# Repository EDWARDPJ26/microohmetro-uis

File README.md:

# Micro-ohmímetro de precisión (1 mΩ – 1 Ω) — versión 2

Proyecto de la asignatura **Diseño de Sistemas Electrónicos** de la Universidad Industrial de Santander (E3T), dictada por el profesor Jaime Barrero.
Autores: **Edward Andrés Pacheco Jurado** (2222236) y **Joseph Thomas Albarracín Contreras** (2220415), 2026.

Es un instrumento portátil con medición Kelvin de 4 hilos. Usa **corriente pulsada de dos niveles (1,042 A / 0,502 A)** y **medición ratiométrica**, con un ADC sigma-delta **AD7124-4** que aprovecha su PGA. El control lo hace un **ESP32-C3**, con BLE y OTA. Se alimenta de una **LiPo 1S de 2000 mAh** integrada en la PCB, que se carga por **USB-C Power Delivery** con un **BQ25895**.

## Contenido del repositorio
| Carpeta | Contenido |
|---|---|
| [`informe/`](informe/) | **Informe final** en PDF y su fuente LaTeX (`main.tex` y figuras) |
| [`hardware/kicad/`](hardware/kicad/) | Proyecto KiCad 10: esquemático jerárquico de 9 hojas, PCB de 4 capas, librería propia y scripts generadores (`gen/`) |
| [`hardware/fabricacion/`](hardware/fabricacion/) | Gerbers con taladros (ZIP), archivo de posiciones (pick & place) y modelo **STEP** |
| [`simulaciones/`](simulaciones/) | Netlists PSpice (`.cir`, `circuito_v2.inc`), datos `.csv` y resumen de resultados |
| [`imagenes/`](imagenes/) | Esquemáticos en SVG/PDF, renders 3D, plano acotado y capas de cobre |
| [`docs/`](docs/) | Diseño detallado (B1), BOM, resumen del esquemático (B3) e informes de las etapas 1–7 |

## Cómo abrir y verificar
- **Esquemático y PCB:** abrir `hardware/kicad/microohmetro_v2.kicad_pro` en **KiCad 10**. La librería propia se carga sola desde `Librerias/` gracias a `sym-lib-table`.
- **Regenerar el esquemático o la PCB:** `python gen/gen_sch3.py` y `python gen/gen_pcb.py`, con el Python que trae KiCad.
- **Simulaciones:** `psp_cmd.exe <archivo>.cir` (Cadence PSpice 22.1). **Los modelos de TI no se redistribuyen**; descárgalos y colócalos en `simulaciones/modelos/`:
  - OPA4388 (equivalente al OPA388): https://www.ti.com/lit/zip/sbomaz6 → `modelos/opa4388_pspice/OPA4388.LIB`
  - INA181A1: https://www.ti.com/lit/zip/sbombb7 → `modelos/ina181a1_pspice/ina181a1.lib`
- **Informe:** subir `informe/` a Overleaf (pdfLaTeX).

## Resultados principales
| Ítem | Valor |
|---|---|
| Error DC ratiométrico simulado | −0,0054 % (sistemático, se calibra) |
| FEM de ±10 µV | ±0,96 % con un nivel → **0 %** con dos niveles |
| Montecarlo, shunt 0,1 % | σ = **0,057 %** (diseño anterior: σ = 88 %) |
| PCB | 4 capas, **64 × 116 mm**, batería en la cara inferior |

**Estado de la PCB:** el DRC no reporta cortocircuitos ni violaciones de holgura. Quedan **unas 7 conexiones cortas por rutear** a mano antes de fabricar: VBUS_C, +3V3, SYS, PMID e I2C_SDA.

## Datasheets de los componentes principales
- [AD7124-4](https://www.analog.com/media/en/technical-documentation/data-sheets/ad7124-4.pdf)
- [REF3325](https://www.ti.com/lit/ds/symlink/ref3325.pdf)
- [OPA388](https://www.ti.com/lit/ds/symlink/opa388.pdf)
- [INA181](https://www.ti.com/lit/ds/symlink/ina181.pdf)
- [BQ25895](https://www.ti.com/lit/ds/symlink/bq25895.pdf)
- [STUSB4500](https://www.st.com/resource/en/datasheet/stusb4500.pdf)
- [ESP32-C3-WROOM-02](https://www.espressif.com/sites/default/files/documentation/esp32-c3-wroom-02_datasheet_en.pdf)
- [AP2112](https://www.diodes.com/assets/Datasheets/AP2112.pdf)
- [NTD25P03L](https://www.onsemi.com/pdf/datasheet/ntd25p03l-d.pdf)
- [WSK2512](https://www.vishay.com/docs/30108/wsk2512.pdf)
- [AO3401A](https://www.aosmd.com/res/datasheets/AO3401A.pdf)
- [USBLC6-2](https://www.st.com/resource/en/datasheet/usblc6-2.pdf)

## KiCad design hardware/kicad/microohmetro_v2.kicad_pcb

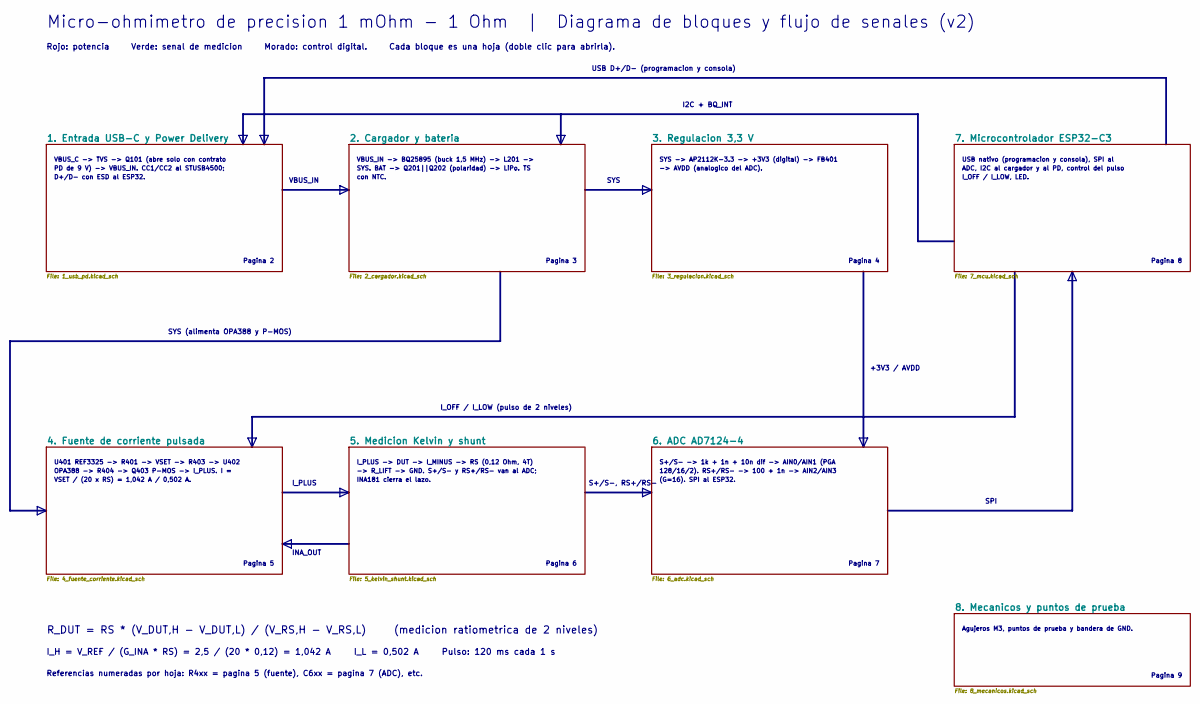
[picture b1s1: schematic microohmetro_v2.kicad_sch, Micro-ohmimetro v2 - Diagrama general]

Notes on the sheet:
VBUS_C -> TVS -> Q101 (abre solo con contrato
PD de 9 V) -> VBUS_IN. CC1/CC2 al STUSB4500;
D+/D- con ESD al ESP32.
Pagina 2
VBUS_IN -> BQ25895 (buck 1,5 MHz) -> L201 ->
SYS. BAT -> Q201||Q202 (polaridad) -> LiPo. TS
con NTC.
Pagina 3
SYS -> AP2112K-3.3 -> +3V3 (digital) -> FB401
-> AVDD (analogico del ADC).
Pagina 4
U401 REF3325 -> R401 -> VSET -> R403 -> U402
OPA388 -> R404 -> Q403 P-MOS -> I_PLUS. I =
VSET / (20 x RS) = 1,042 A / 0,502 A.
Pagina 5
I_PLUS -> DUT -> I_MINUS -> RS (0,12 Ohm, 4T)
-> R_LIFT -> GND. S+/S- y RS+/RS- van al ADC;
INA181 cierra el lazo.
Pagina 6
S+/S- -> 1k + 1n + 10n dif -> AIN0/AIN1 (PGA
128/16/2). RS+/RS- -> 100 + 1n -> AIN2/AIN3
(G=16). SPI al ESP32.
Pagina 7
USB nativo (programacion y consola), SPI al
ADC, I2C al cargador y al PD, control del pulso
I_OFF / I_LOW, LED.
Pagina 8
Agujeros M3, puntos de prueba y bandera de GND.
Pagina 9
VBUS_IN
SYS
SYS (alimenta OPA388 y P-MOS)
+3V3 / AVDD
I_PLUS
INA_OUT
S+/S-, RS+/RS-
SPI
I_OFF / I_LOW (pulso de 2 niveles)
I2C + BQ_INT
USB D+/D- (programacion y consola)

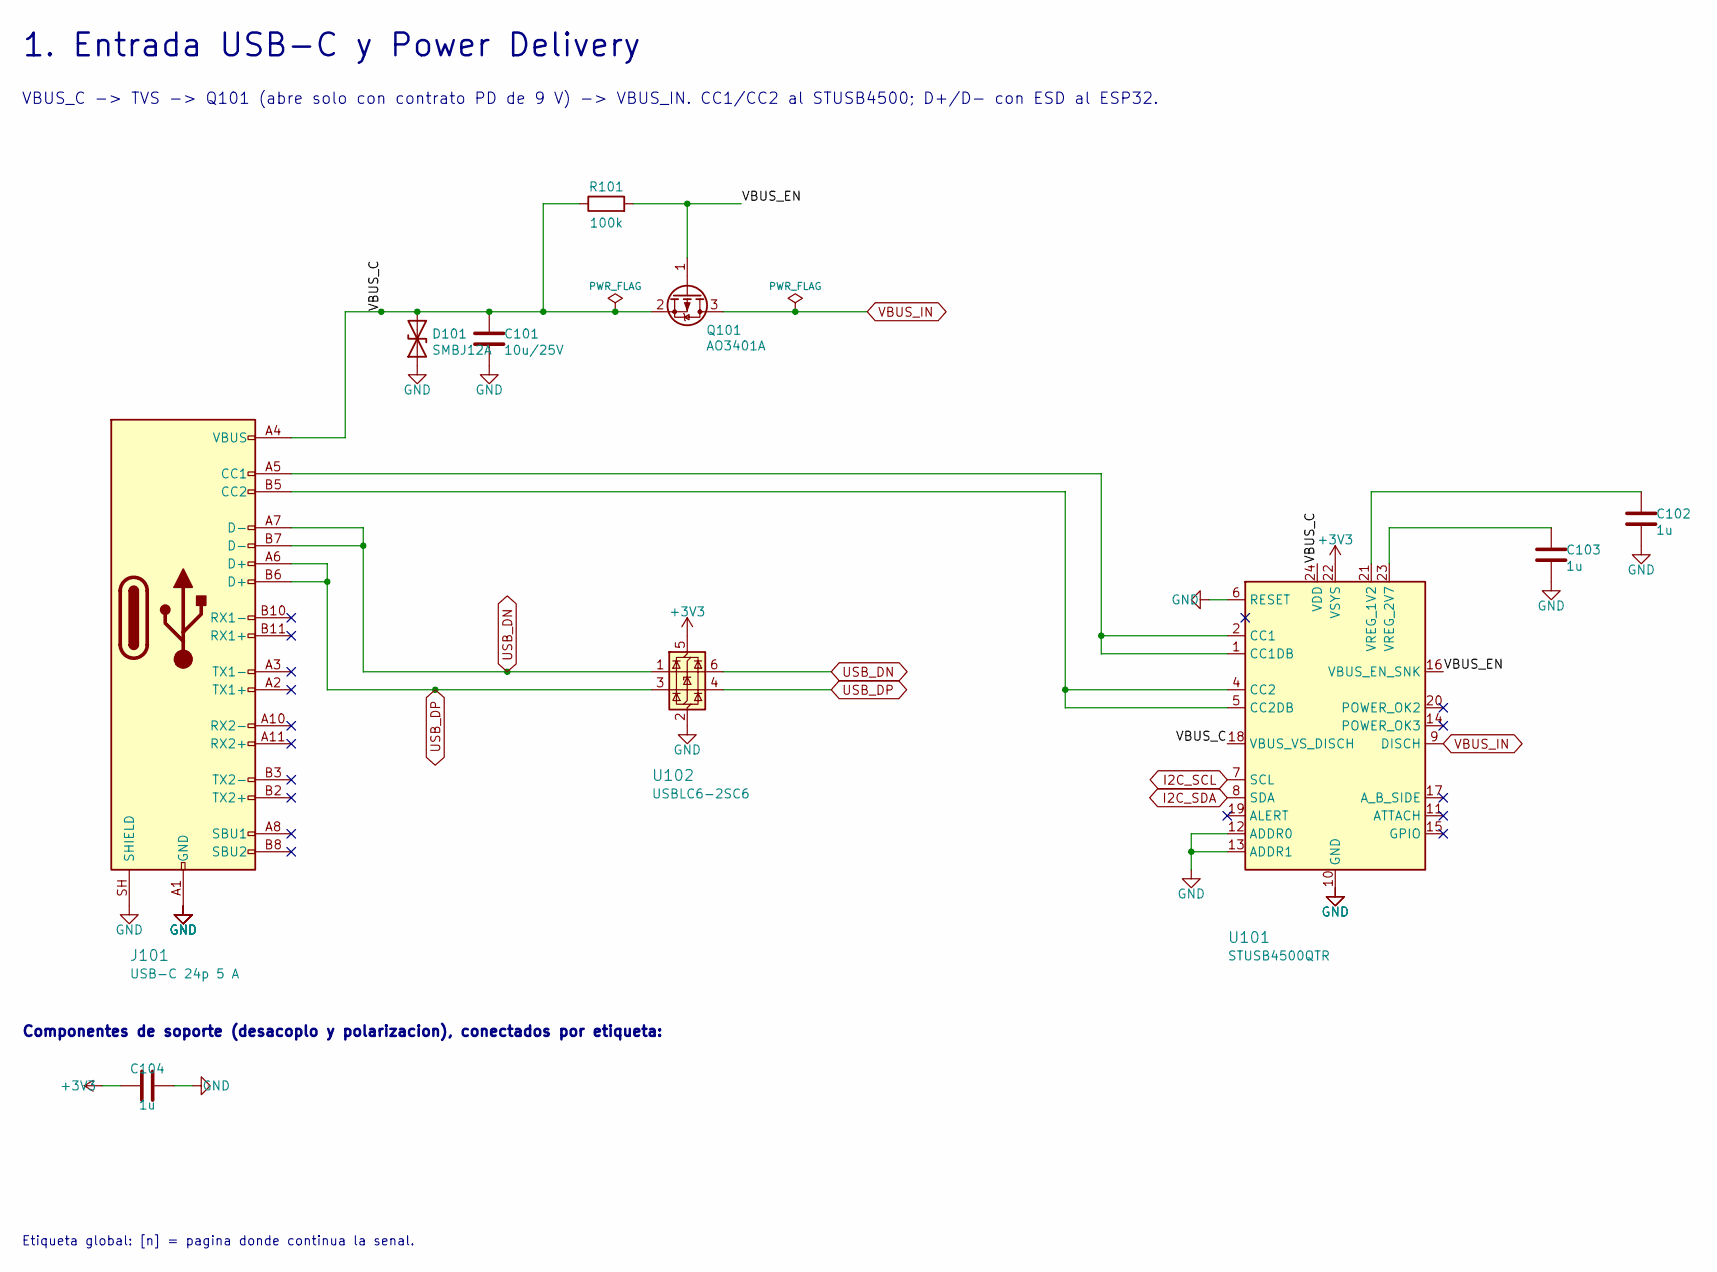
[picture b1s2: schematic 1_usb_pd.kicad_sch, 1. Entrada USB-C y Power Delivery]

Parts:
C101: 10u/25V; C_0805_2012Metric
C102, C103, C104: 1u; C_0603_1608Metric
D101: SMBJ12A; D_SMB; MPN SMBJ12A
J101: USB-C 24p 5 A; USB_C_Receptacle_Amphenol_12401610E4-2A; MPN Amphenol 12401610E4#2A
Q101: AO3401A; SOT-23; MPN AO3401A
R101: 100k; R_0603_1608Metric
U101: STUSB4500QTR; QFN-24-1EP_4x4mm_P0.5mm_EP2.7x2.7mm; MPN STUSB4500QTR
U102: USBLC6-2SC6; SOT-23-6; MPN USBLC6-2SC6

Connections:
+3V3: C104.1, U101.22 (VSYS), U102.5 (VBUS); also elsewhere on the board
GND: C101.2, C102.2, C103.2, C104.2, D101.1 (A1), J101.A1 (GND), J101.A12 (GND), J101.B1 (GND), J101.B12 (GND), J101.SH (SHIELD), U101.6 (RESET), U101.10 (GND), U101.12 (ADDR0), U101.13 (ADDR1), U101.25 (GND), U102.2 (GND); also elsewhere on the board
I2C_SCL: U101.7 (SCL); also elsewhere on the board
I2C_SDA: U101.8 (SDA); also elsewhere on the board
unnamed: J101.A5 (CC1), U101.1 (CC1DB), U101.2 (CC1)
unnamed: J101.B5 (CC2), U101.4 (CC2), U101.5 (CC2DB)
unnamed: C102.1, U101.21 (VREG_1V2)
unnamed: C103.1, U101.23 (VREG_2V7)
USB_DN: J101.A7 (D-), J101.B7 (D-), U102.1 (I/O1), U102.6 (I/O1); also elsewhere on the board
USB_DP: J101.A6 (D+), J101.B6 (D+), U102.3 (I/O2), U102.4 (I/O2); also elsewhere on the board
VBUS_C: C101.1, D101.2 (A2), J101.A4 (VBUS), J101.A9 (VBUS), J101.B4 (VBUS), J101.B9 (VBUS), Q101.2 (S), R101.1, U101.18 (VBUS_VS_DISCH), U101.24 (VDD)
VBUS_EN: Q101.1 (G), R101.2, U101.16 (VBUS_EN_SNK)
VBUS_IN: Q101.3 (D), U101.9 (DISCH); also elsewhere on the board

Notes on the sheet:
1. Entrada USB-C y Power Delivery
VBUS_C -> TVS -> Q101 (abre solo con contrato PD de 9 V) -> VBUS_IN. CC1/CC2 al STUSB4500; D+/D- con ESD al ESP32.
Componentes de soporte (desacoplo y polarizacion), conectados por etiqueta:
Etiqueta global: [n] = pagina donde continua la senal.

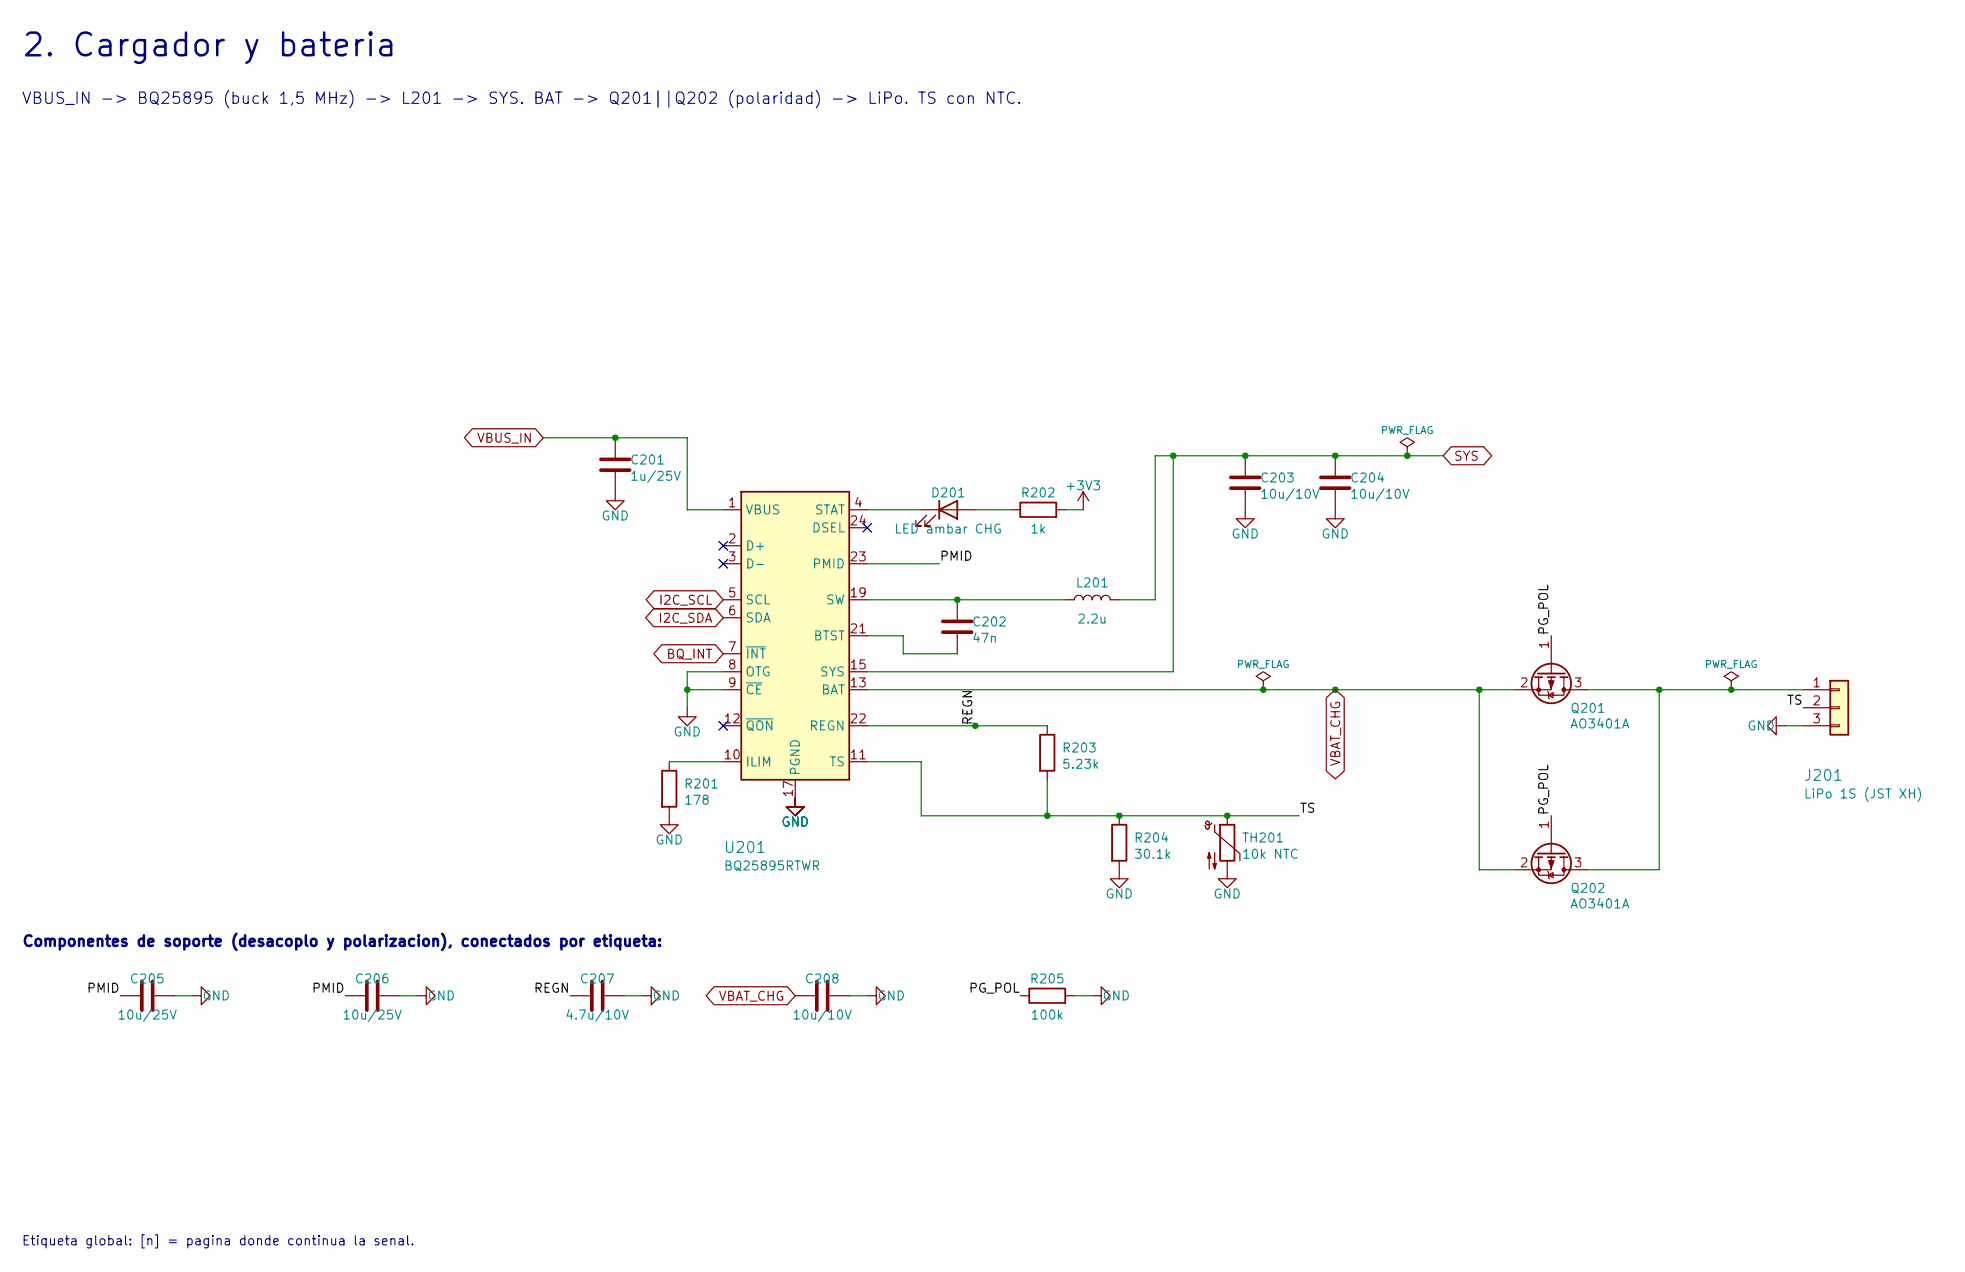
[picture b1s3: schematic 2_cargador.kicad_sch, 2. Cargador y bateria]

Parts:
C201: 1u/25V; C_0603_1608Metric
C202: 47n; C_0603_1608Metric
C203, C204, C208: 10u/10V; C_0805_2012Metric
C205, C206: 10u/25V; C_0805_2012Metric
C207: 4.7u/10V; C_0603_1608Metric
D201: LED ambar CHG; LED_0603_1608Metric
J201: LiPo 1S (JST XH); JST_XH_S3B-XH-SM4-TB_1x03-1MP_P2.50mm_Horizontal; MPN S3B-XH-SM4-TB
L201: 2.2u; L_Bourns-SRN4018; MPN SRN4018-2R2M
Q201, Q202: AO3401A; SOT-23; MPN AO3401A
R201: 178; R_0603_1608Metric
R202: 1k; R_0603_1608Metric
R203: 5.23k; R_0603_1608Metric
R204: 30.1k; R_0603_1608Metric
R205: 100k; R_0603_1608Metric
TH201: 10k NTC; R_0603_1608Metric; MPN NCP18XH103F03RB
U201: BQ25895RTWR; Texas_RTW_WQFN-24-1EP_4x4mm_P0.5mm_EP2.7x2.7mm_ThermalVias; MPN BQ25895RTWR

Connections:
+3V3: R202.2; also elsewhere on the board
BQ_INT: U201.7 (~INT); also elsewhere on the board
GND: C201.2, C203.2, C204.2, C205.2, C206.2, C207.2, C208.2, J201.3, R201.2, R204.2, R205.2, TH201.2, U201.8 (OTG), U201.9 (~CE), U201.17 (PGND), U201.18 (PGND), U201.25 (PGND); also elsewhere on the board
I2C_SCL: U201.5 (SCL); also elsewhere on the board
I2C_SDA: U201.6 (SDA); also elsewhere on the board
unnamed: C202.1, L201.1, U201.19 (SW), U201.20 (SW)
unnamed: D201.2 (A), R202.1
unnamed: D201.1 (K), U201.4 (STAT)
unnamed: J201.1, Q201.3 (D), Q202.3 (D)
unnamed: C202.2, U201.21 (BTST)
unnamed: R201.1, U201.10 (ILIM)
PG_POL: Q201.1 (G), Q202.1 (G), R205.1
PMID: C205.1, C206.1, U201.23 (PMID)
REGN: C207.1, R203.1, U201.22 (REGN)
SYS: C203.1, C204.1, L201.2, U201.15 (SYS), U201.16 (SYS); also elsewhere on the board
TS: J201.2, R203.2, R204.1, TH201.1, U201.11 (TS)
VBAT_CHG: C208.1, Q201.2 (S), Q202.2 (S), U201.13 (BAT), U201.14 (BAT); also elsewhere on the board
VBUS_IN: C201.1, U201.1 (VBUS); also elsewhere on the board

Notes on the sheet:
2. Cargador y bateria
VBUS_IN -> BQ25895 (buck 1,5 MHz) -> L201 -> SYS. BAT -> Q201||Q202 (polaridad) -> LiPo. TS con NTC.
Componentes de soporte (desacoplo y polarizacion), conectados por etiqueta:
Etiqueta global: [n] = pagina donde continua la senal.

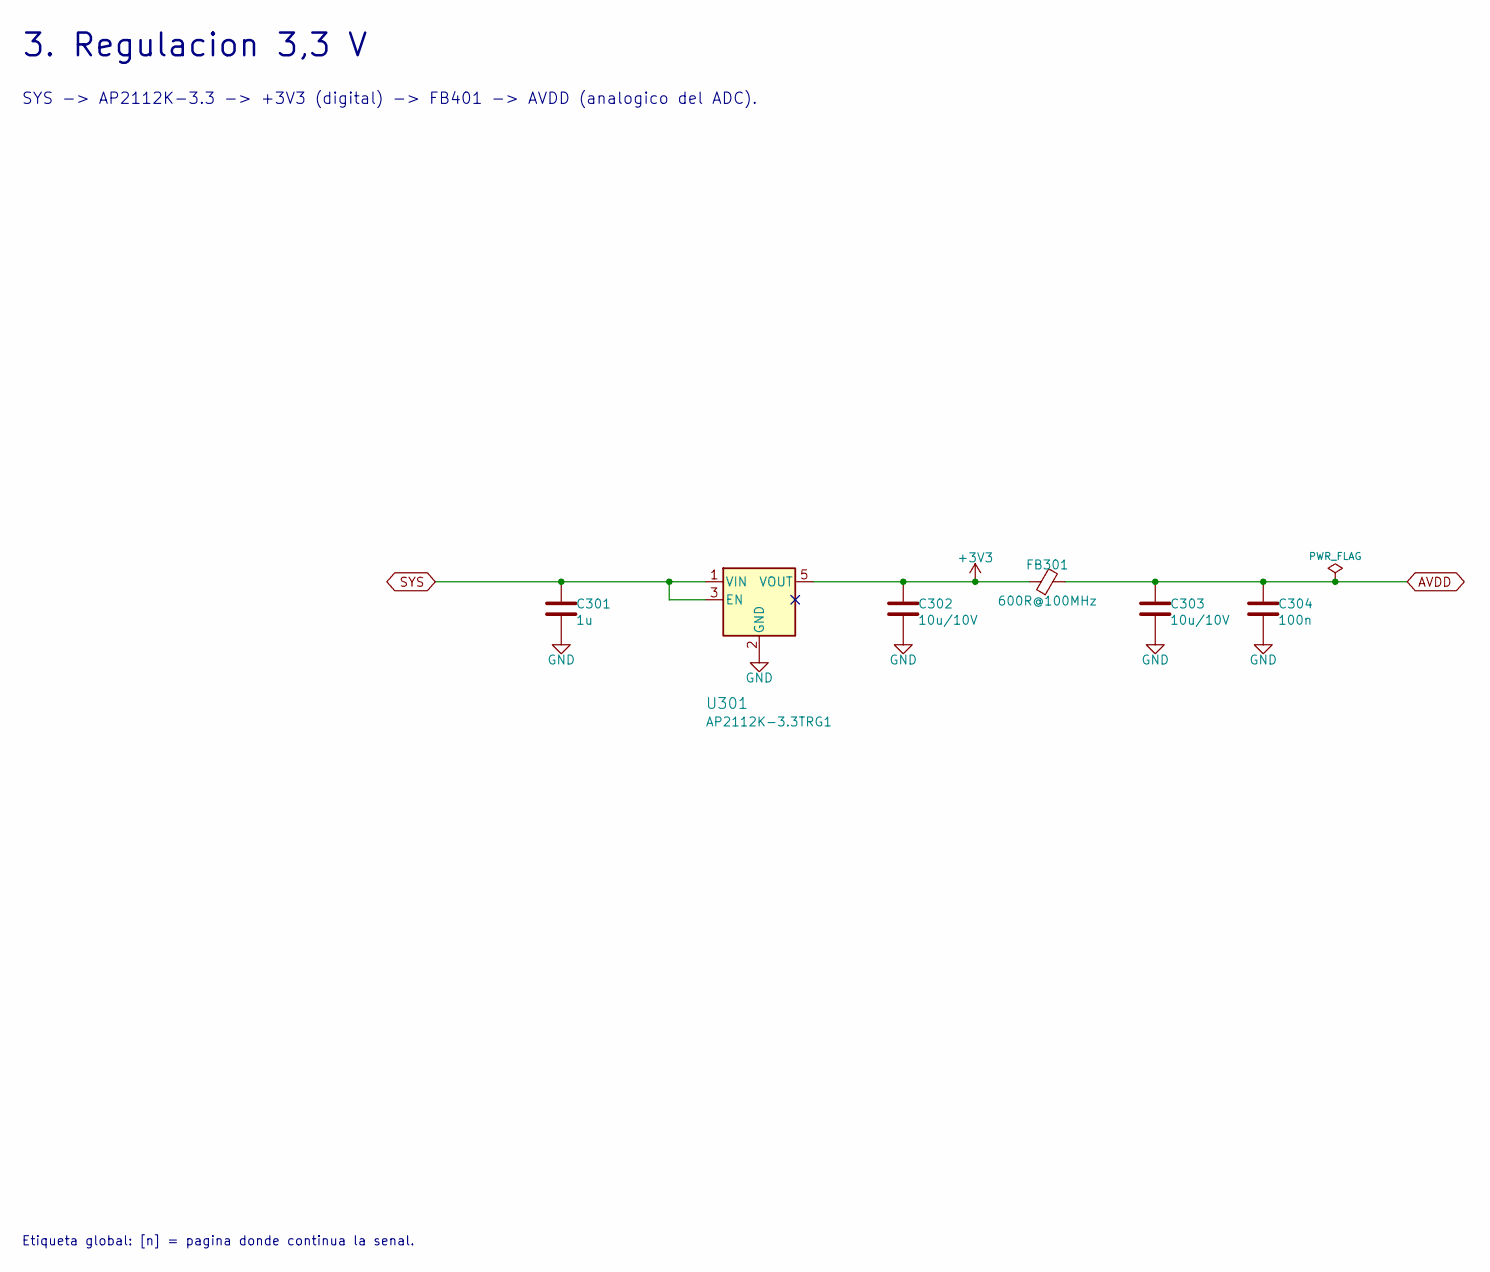
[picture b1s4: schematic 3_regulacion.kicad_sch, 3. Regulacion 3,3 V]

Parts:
C301: 1u; C_0603_1608Metric
C302, C303: 10u/10V; C_0805_2012Metric
C304: 100n; C_0603_1608Metric
FB301: 600R@100MHz; L_0603_1608Metric; MPN BLM18KG601SN1D
U301: AP2112K-3.3TRG1; SOT-23-5; MPN AP2112K-3.3TRG1

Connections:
+3V3: C302.1, FB301.1, U301.5 (VOUT); also elsewhere on the board
AVDD: C303.1, C304.1, FB301.2; also elsewhere on the board
GND: C301.2, C302.2, C303.2, C304.2, U301.2 (GND); also elsewhere on the board
SYS: C301.1, U301.1 (VIN), U301.3 (EN); also elsewhere on the board

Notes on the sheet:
3. Regulacion 3,3 V
SYS -> AP2112K-3.3 -> +3V3 (digital) -> FB401 -> AVDD (analogico del ADC).
Etiqueta global: [n] = pagina donde continua la senal.

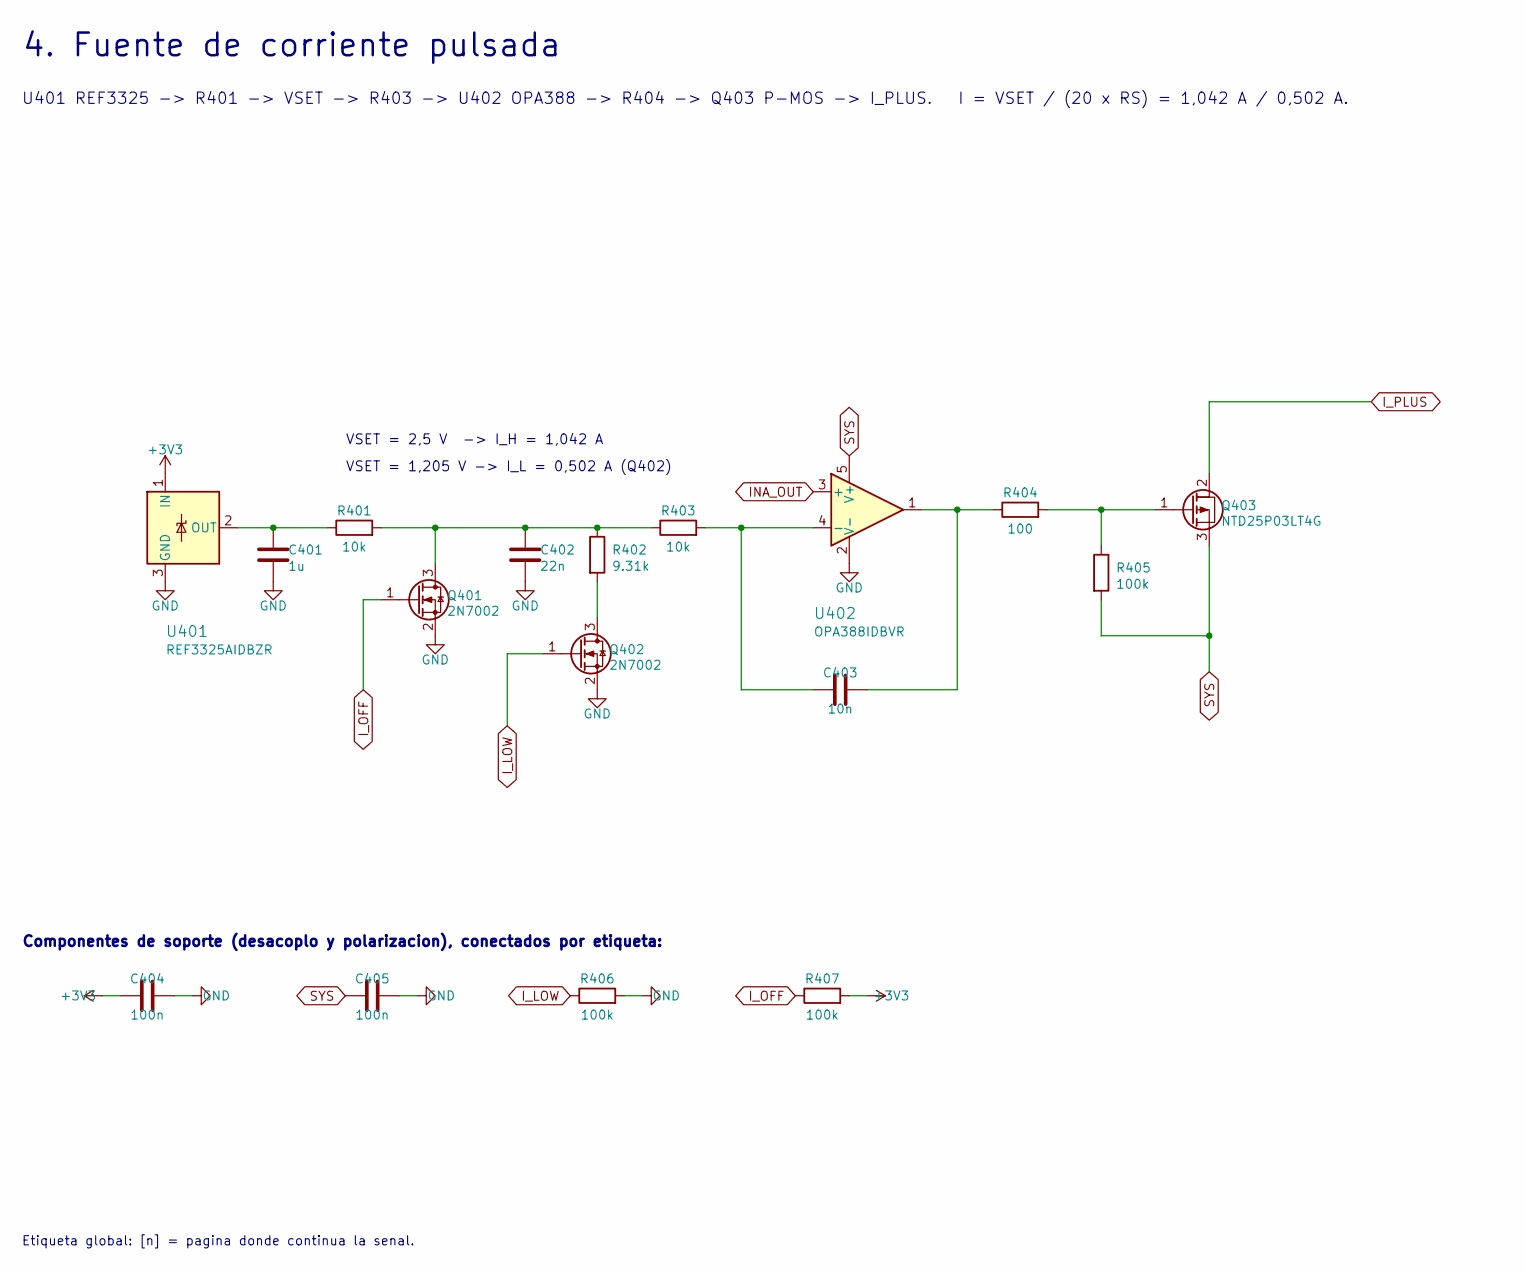
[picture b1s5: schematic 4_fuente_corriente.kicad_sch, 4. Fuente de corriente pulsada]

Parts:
C401: 1u; C_0603_1608Metric
C402: 22n; C_0603_1608Metric
C403: 10n; C_0603_1608Metric
C404, C405: 100n; C_0603_1608Metric
Q401, Q402: 2N7002; SOT-23; MPN 2N7002
Q403: NTD25P03LT4G; TO-252-2; MPN NTD25P03LT4G
R401, R403: 10k; R_0603_1608Metric
R402: 9.31k; R_0603_1608Metric
R404: 100; R_0603_1608Metric
R405, R406, R407: 100k; R_0603_1608Metric
U401: REF3325AIDBZR; SOT-23; MPN REF3325AIDBZR
U402: OPA388IDBVR; SOT-23-5; MPN OPA388IDBVR

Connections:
+3V3: C404.1, R407.2, U401.1 (IN); also elsewhere on the board
GND: C401.2, C402.2, C404.2, C405.2, Q401.2 (S), Q402.2 (S), R406.2, U401.3 (GND), U402.2 (V-); also elsewhere on the board
INA_OUT: U402.3 (+); also elsewhere on the board
I_LOW: Q402.1 (G), R406.1; also elsewhere on the board
I_OFF: Q401.1 (G), R407.1; also elsewhere on the board
I_PLUS: Q403.2 (D); also elsewhere on the board
unnamed: C403.2, R404.1, U402.1
unnamed: C402.1, Q401.3 (D), R401.2, R402.1, R403.1
unnamed: Q402.3 (D), R402.2
unnamed: Q403.1 (G), R404.2, R405.1
unnamed: C401.1, R401.1, U401.2 (OUT)
unnamed: C403.1, R403.2, U402.4 (-)
SYS: C405.1, Q403.3 (S), R405.2, U402.5 (V+); also elsewhere on the board

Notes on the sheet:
VSET = 2,5 V -> I_H = 1,042 A
VSET = 1,205 V -> I_L = 0,502 A (Q402)
4. Fuente de corriente pulsada
U401 REF3325 -> R401 -> VSET -> R403 -> U402 OPA388 -> R404 -> Q403 P-MOS -> I_PLUS. I = VSET / (20 x RS) = 1,042 A / 0,502 A.
Componentes de soporte (desacoplo y polarizacion), conectados por etiqueta:
Etiqueta global: [n] = pagina donde continua la senal.

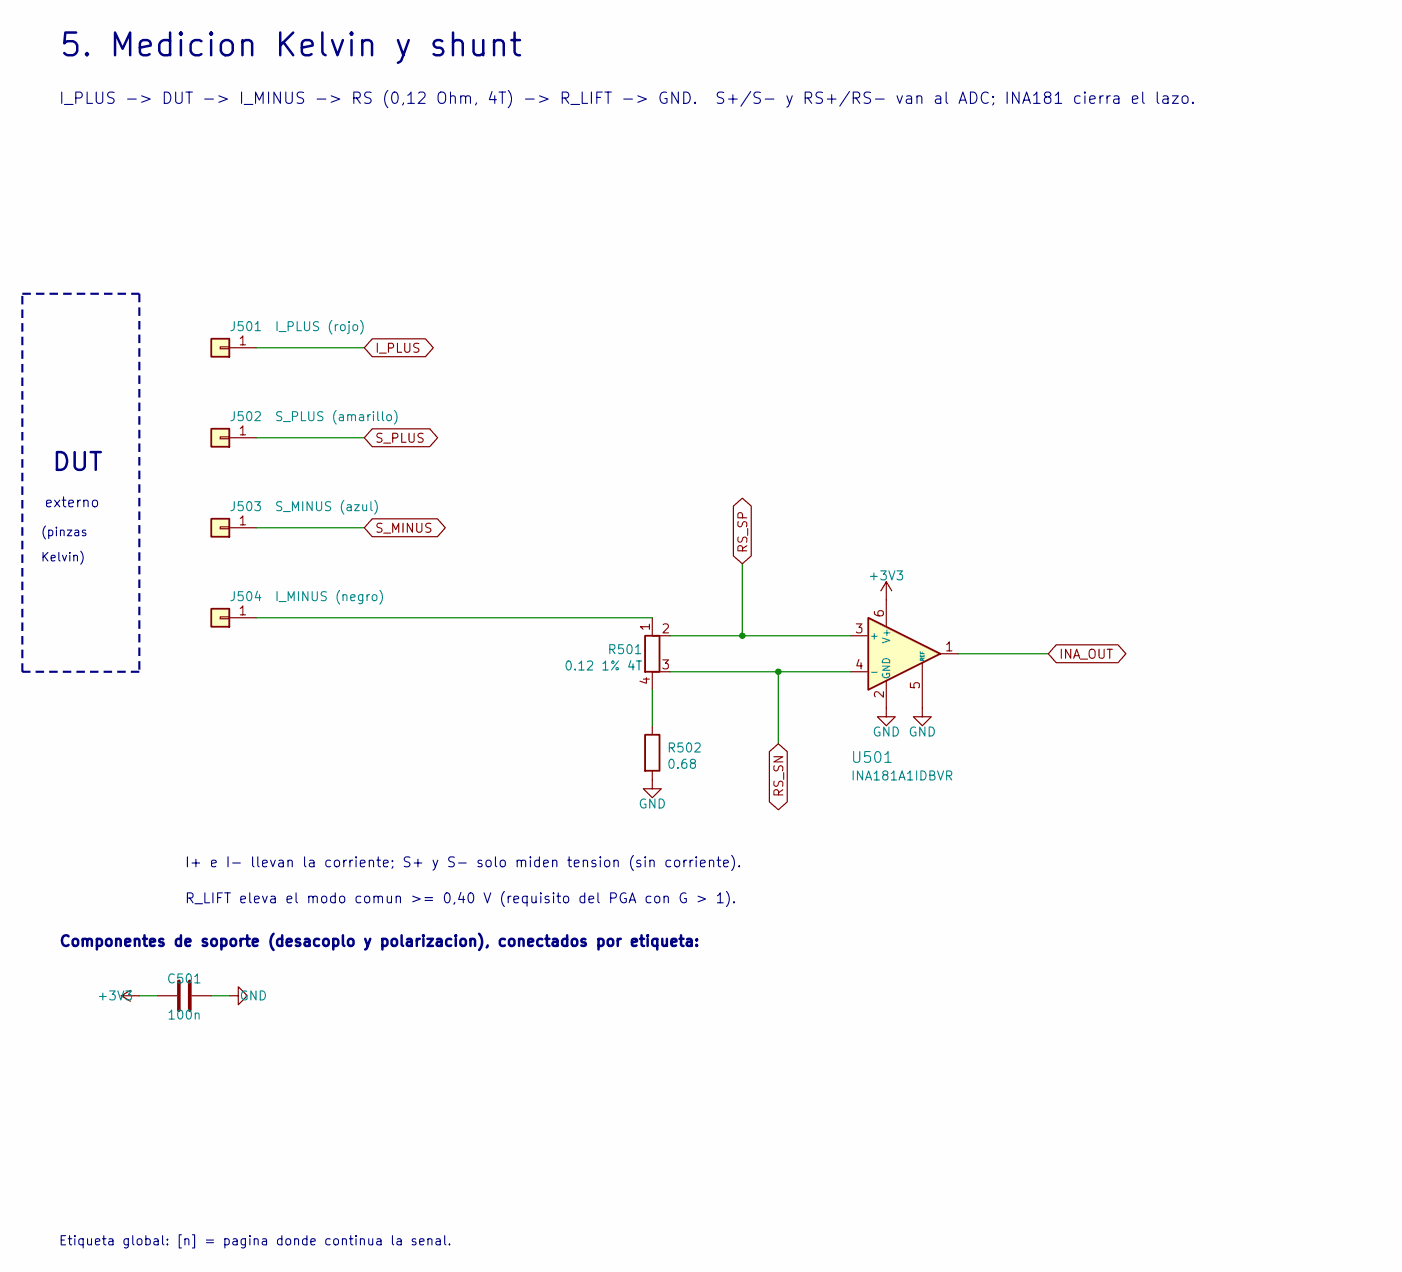
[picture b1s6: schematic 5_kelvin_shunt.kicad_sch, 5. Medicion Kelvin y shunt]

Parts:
C501: 100n; C_0603_1608Metric
J501: I_PLUS (rojo); Banana_Jack_1Pin; MPN Borne 4 mm de panel rojo (agujero 6 mm)
J502: S_PLUS (amarillo); Banana_Jack_1Pin; MPN Borne 4 mm de panel amarillo (agujero 6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
J503: S_MINUS (azul); Banana_Jack_1Pin; MPN Borne 4 mm de panel azul (agujero 6 mm)
J504: I_MINUS (negro); Banana_Jack_1Pin; MPN Borne 4 mm de panel negro (agujero 6 mm)
R501: 0.12 1% 4T; R_Shunt_Vishay_WSK2512_6332Metric_T1.19mm; MPN WSK2512R1200FEA
R502: 0.68; R_2512_6332Metric
U501: INA181A1IDBVR; SOT-23-6; MPN INA181A1IDBVR

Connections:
+3V3: C501.1, U501.6 (V+); also elsewhere on the board
GND: C501.2, R502.2, U501.2 (GND), U501.5 (REF); also elsewhere on the board
INA_OUT: U501.1; also elsewhere on the board
I_PLUS: J501.1; also elsewhere on the board
unnamed: J504.1, R501.1
unnamed: R501.4, R502.1
RS_SN: R501.3, U501.4 (-); also elsewhere on the board
RS_SP: R501.2, U501.3 (+); also elsewhere on the board
S_MINUS: J503.1; also elsewhere on the board
S_PLUS: J502.1; also elsewhere on the board

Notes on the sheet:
DUT
externo
(pinzas
Kelvin)
I+ e I- llevan la corriente; S+ y S- solo miden tension (sin corriente).
R_LIFT eleva el modo comun >= 0,40 V (requisito del PGA con G > 1).
5. Medicion Kelvin y shunt
I_PLUS -> DUT -> I_MINUS -> RS (0,12 Ohm, 4T) -> R_LIFT -> GND. S+/S- y RS+/RS- van al ADC; INA181 cierra el lazo.
Componentes de soporte (desacoplo y polarizacion), conectados por etiqueta:
Etiqueta global: [n] = pagina donde continua la senal.

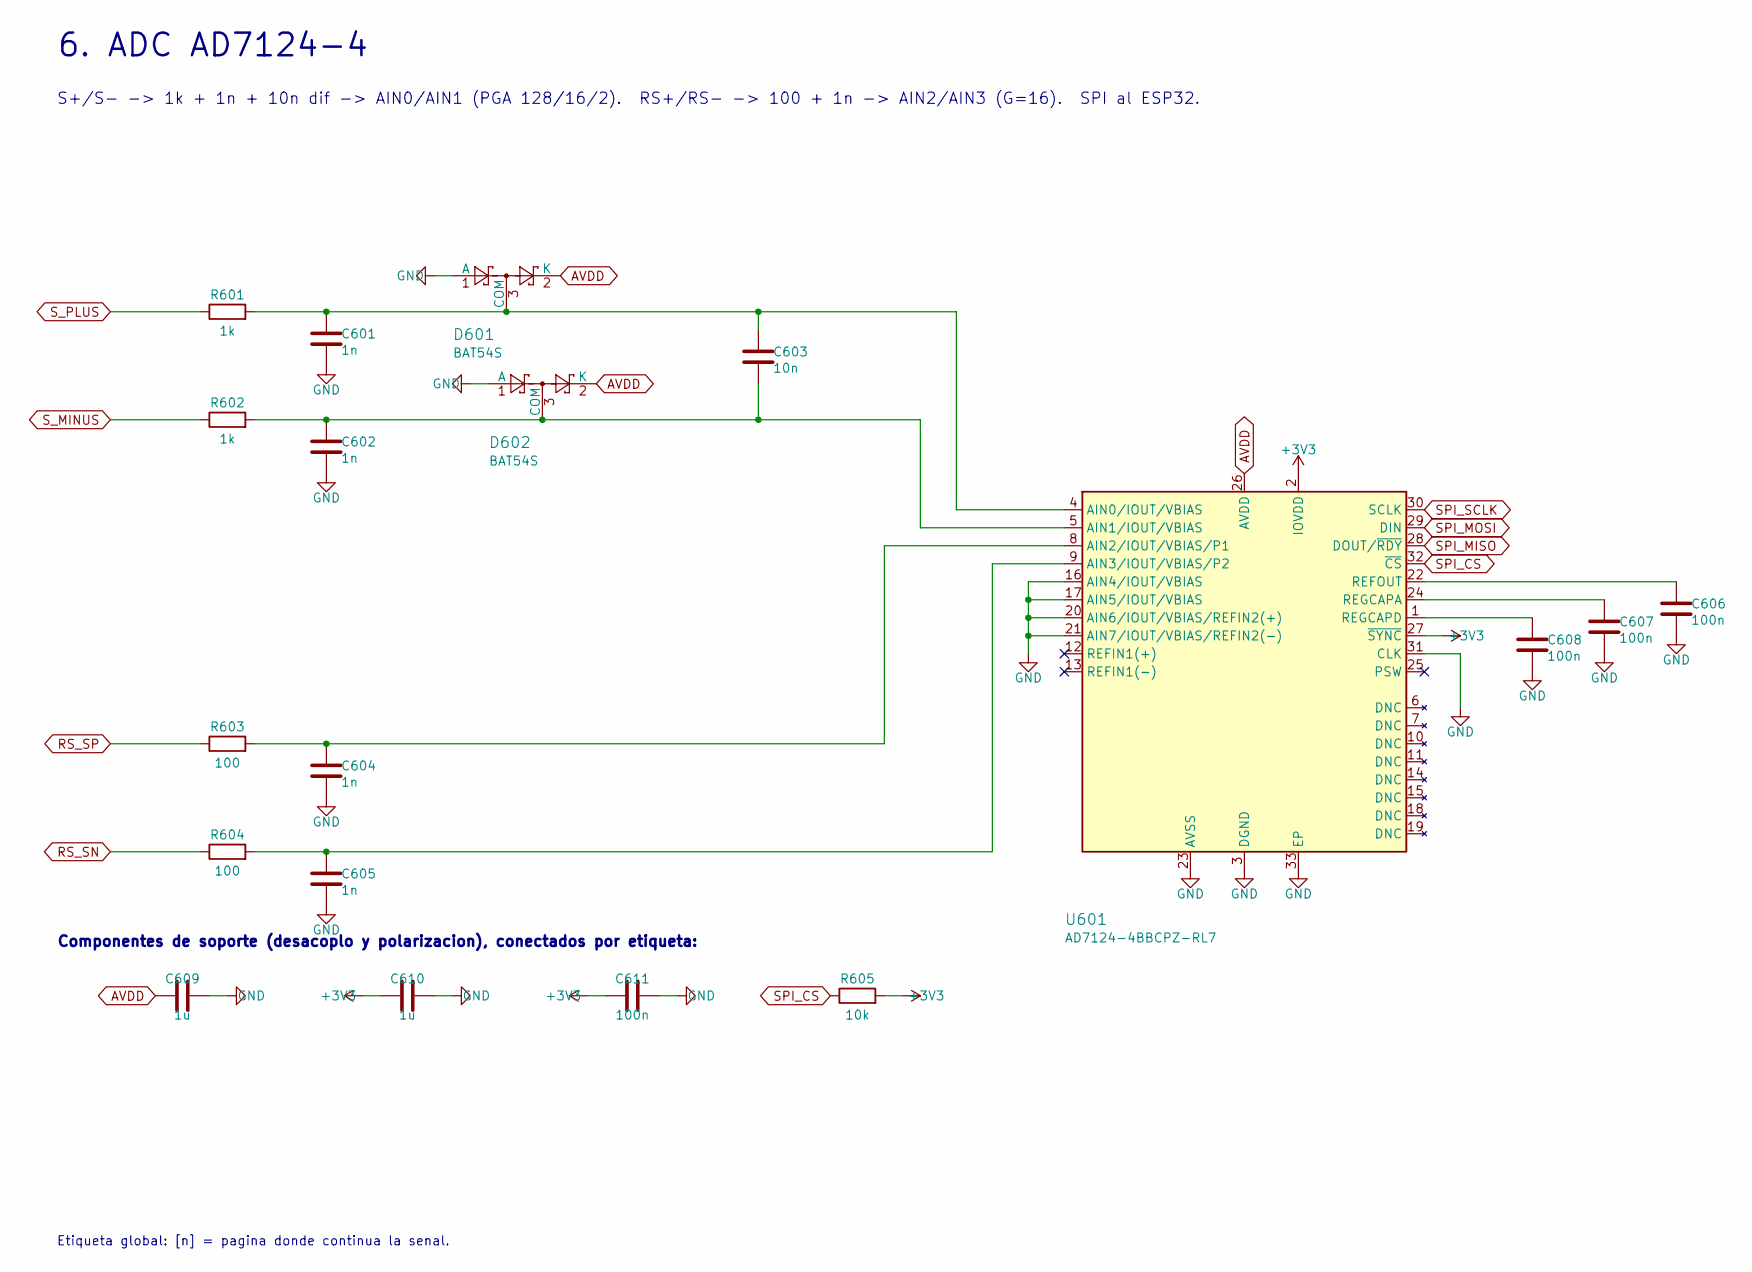
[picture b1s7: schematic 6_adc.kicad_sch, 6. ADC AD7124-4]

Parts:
C601, C602, C604, C605: 1n; C_0603_1608Metric
C603: 10n; C_0603_1608Metric
C606, C607, C608, C611: 100n; C_0603_1608Metric
C609, C610: 1u; C_0603_1608Metric
D601, D602: BAT54S; SOT-23; MPN BAT54S
R601, R602: 1k; R_0603_1608Metric
R603, R604: 100; R_0603_1608Metric
R605: 10k; R_0603_1608Metric
U601: AD7124-4BBCPZ-RL7; LFCSP-32-1EP_5x5mm_P0.5mm_EP3.6x3.6mm; MPN AD7124-4BBCPZ-RL7

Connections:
+3V3: C610.1, C611.1, R605.2, U601.2 (IOVDD), U601.27 (~SYNC); also elsewhere on the board
AVDD: C609.1, D601.2 (K), D602.2 (K), U601.26 (AVDD); also elsewhere on the board
GND: C601.2, C602.2, C604.2, C605.2, C606.2, C607.2, C608.2, C609.2, C610.2, C611.2, D601.1 (A), D602.1 (A), U601.3 (DGND), U601.16 (AIN4/IOUT/VBIAS), U601.17 (AIN5/IOUT/VBIAS), U601.20 (AIN6/IOUT/VBIAS/REFIN2(+)), U601.21 (AIN7/IOUT/VBIAS/REFIN2(-)), U601.23 (AVSS), U601.31 (CLK), U601.33 (EP); also elsewhere on the board
unnamed: C601.1, C603.1, D601.3 (COM), R601.2, U601.4 (AIN0/IOUT/VBIAS)
unnamed: C602.1, C603.2, D602.3 (COM), R602.2, U601.5 (AIN1/IOUT/VBIAS)
unnamed: C604.1, R603.2, U601.8 (AIN2/IOUT/VBIAS/P1)
unnamed: C605.1, R604.2, U601.9 (AIN3/IOUT/VBIAS/P2)
unnamed: C606.1, U601.22 (REFOUT)
unnamed: C607.1, U601.24 (REGCAPA)
unnamed: C608.1, U601.1 (REGCAPD)
RS_SN: R604.1; also elsewhere on the board
RS_SP: R603.1; also elsewhere on the board
SPI_CS: R605.1, U601.32 (~CS); also elsewhere on the board
SPI_MISO: U601.28 (DOUT/~RDY); also elsewhere on the board
SPI_MOSI: U601.29 (DIN); also elsewhere on the board
SPI_SCLK: U601.30 (SCLK); also elsewhere on the board
S_MINUS: R602.1; also elsewhere on the board
S_PLUS: R601.1; also elsewhere on the board

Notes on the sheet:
6. ADC AD7124-4
S+/S- -> 1k + 1n + 10n dif -> AIN0/AIN1 (PGA 128/16/2). RS+/RS- -> 100 + 1n -> AIN2/AIN3 (G=16). SPI al ESP32.
Componentes de soporte (desacoplo y polarizacion), conectados por etiqueta:
Etiqueta global: [n] = pagina donde continua la senal.
